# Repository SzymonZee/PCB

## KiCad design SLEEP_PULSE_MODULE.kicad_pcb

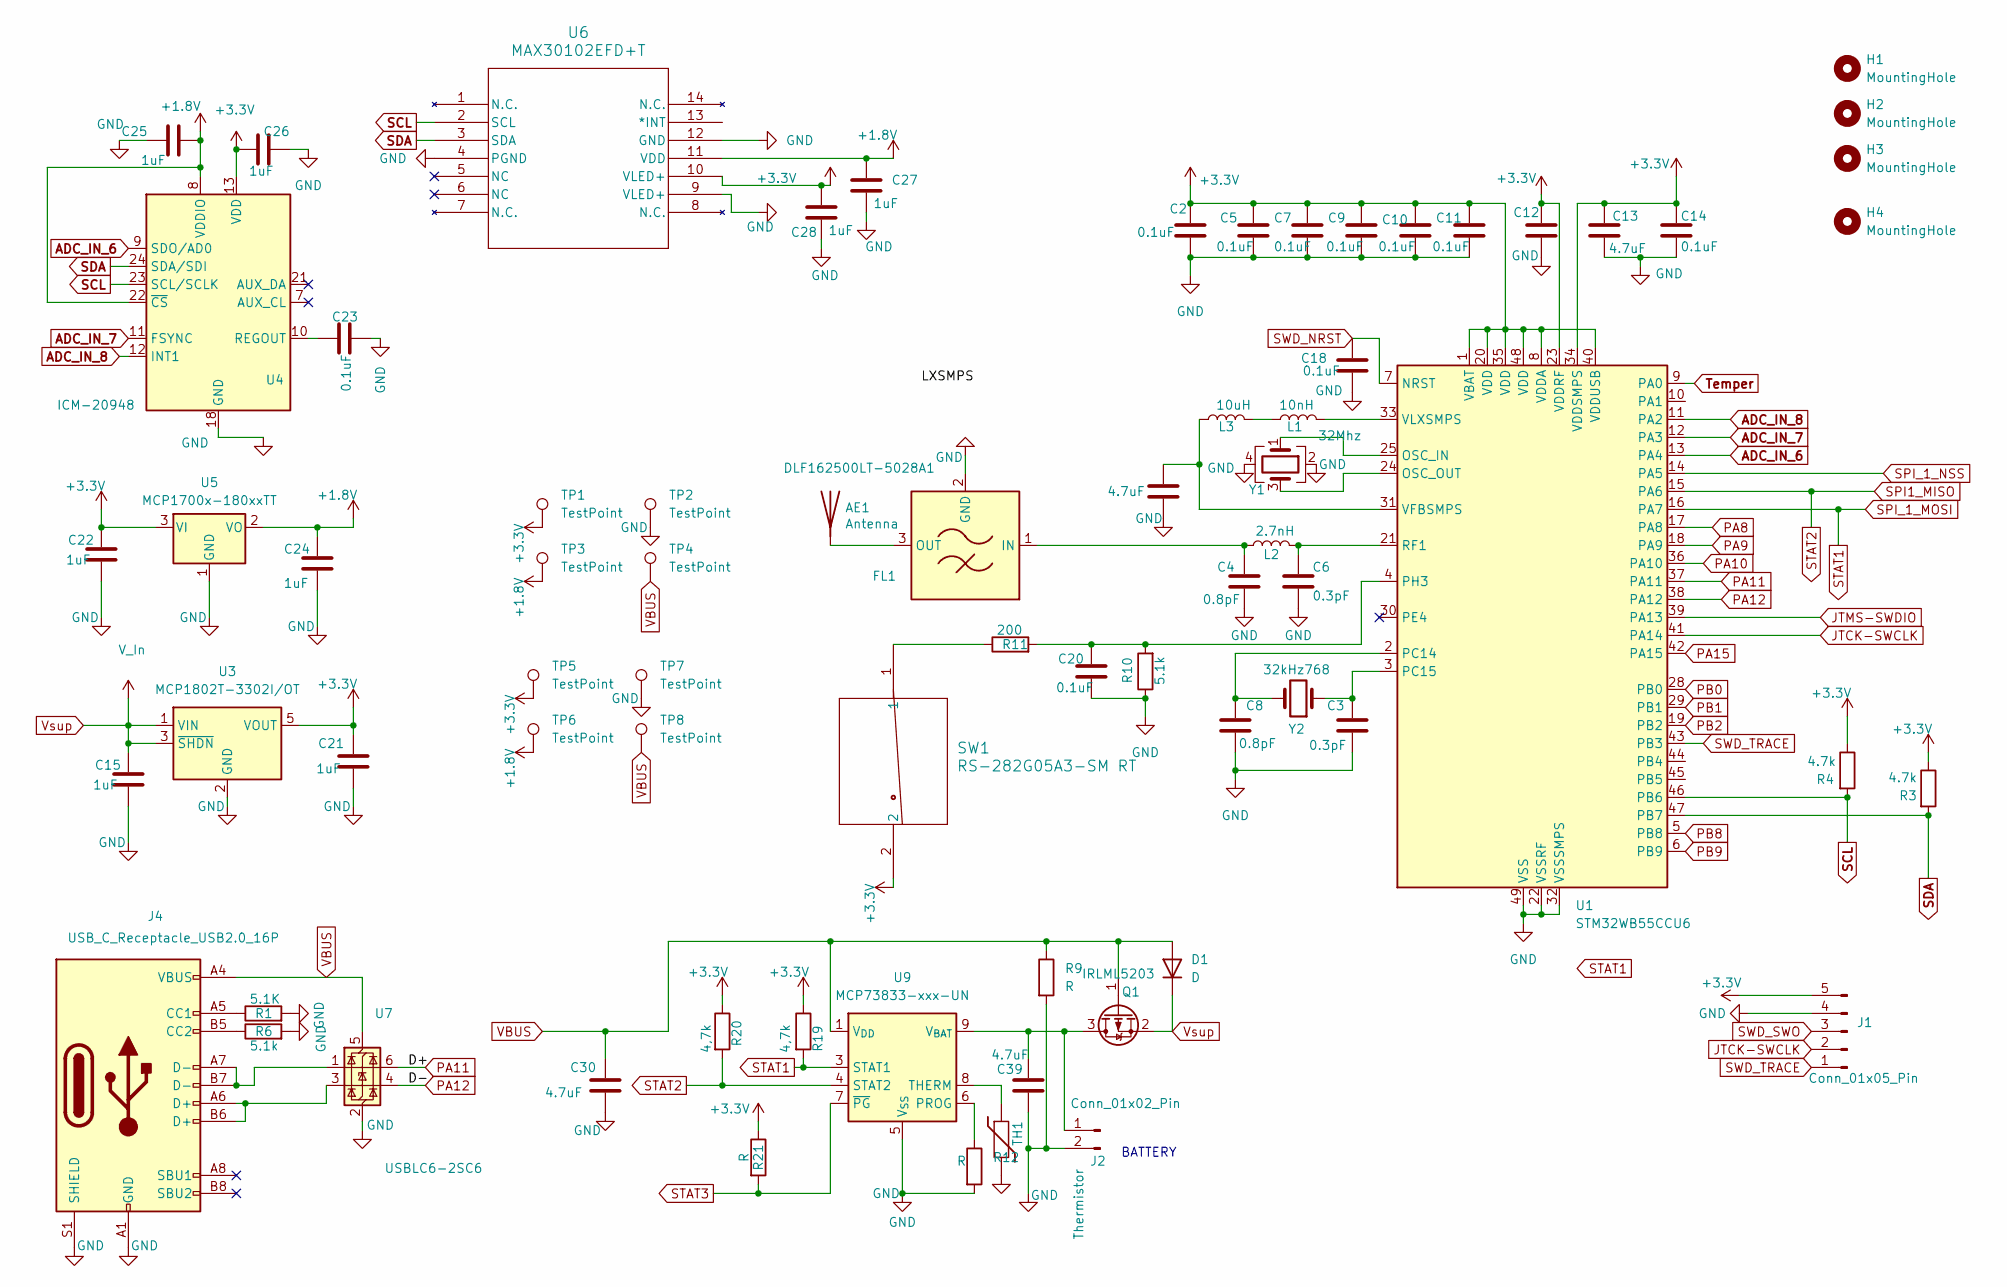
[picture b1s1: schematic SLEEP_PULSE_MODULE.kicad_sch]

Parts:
AE1: Antenna; ANTC3216X140N
C1, C13: 4.7uF; C_0402_1005Metric_Pad0.74x0.62mm_HandSolder
C2, C5, C7, C9, C10, C11, C12, C14, C18, C20, C23: 0.1uF; C_0402_1005Metric_Pad0.74x0.62mm_HandSolder; PARTREV CC0402JRNPO9BN101
C3, C6: 0.3pF; C_0402_1005Metric_Pad0.74x0.62mm_HandSolder
C4, C8: 0.8pF; C_0402_1005Metric_Pad0.74x0.62mm_HandSolder
C15, C21, C22, C24, C25, C26, C27, C28: 1uF; C_0402_1005Metric_Pad0.74x0.62mm_HandSolder
C30, C39: 4.7uF; C_0805_2012Metric_Pad1.18x1.45mm_HandSolder
D1: D; D_SOD-323
FL1: DLF162500LT-5028A1; DLF-4_1P6X0P8
H1, H4: MountingHole; MountingHole_2.2mm_M2
H2, H3: MountingHole
J1: Conn_01x05_Pin
J2: Conn_01x02_Pin; JST_SH_BM02B-SRSS-TB_1x02-1MP_P1.00mm_Vertical
J4: USB_C_Receptacle_USB2.0_16P; USB_C_Receptacle_GCT_USB4105-xx-A_16P_TopMnt_Horizontal
L1: 10nH; C_0402_1005Metric_Pad0.74x0.62mm_HandSolder
L2: 2.7nH; C_0402_1005Metric_Pad0.74x0.62mm_HandSolder
L3: 10uH; L_0805_2012Metric_Pad1.05x1.20mm_HandSolder
Q1: IRLML5203; SOT-23
R1: 5.1K; R_0402_1005Metric_Pad0.72x0.64mm_HandSolder
R3, R4: 4.7k; R_0402_1005Metric_Pad0.72x0.64mm_HandSolder
R6, R10: 5.1k; R_0402_1005Metric_Pad0.72x0.64mm_HandSolder
R9, R12: R; C_0603_1608Metric_Pad1.08x0.95mm_HandSolder
R11: 200; R_0402_1005Metric_Pad0.72x0.64mm_HandSolder
R19, R20: 4,7k; C_0603_1608Metric_Pad1.08x0.95mm_HandSolder
R21: R
SW1: RS-282G05A3-SM RT; RS-282G05A3-SM RT_CNK
TH1: Thermistor; C_0603_1608Metric_Pad1.08x0.95mm_HandSolder
TP1, TP2, TP3, TP4, TP5, TP6, TP7, TP8: TestPoint; TestPoint_Pad_1.0x1.0mm
U1: STM32WB55CCU6; QFN-48-1EP_7x7mm_P0.5mm_EP5.6x5.6mm
U3: MCP1802T-3302I/OT; SOT-23-5
U4: ICM-20948; InvenSense_QFN-24_3x3mm_P0.4mm
U5: MCP1700x-180xxTT; SOT-23
U6: MAX30102EFD+T; 21-1048_F143A5&plus_1_MXM
U7: USBLC6-2SC6; SOT-23-6
U9: MCP73833-xxx-UN; MSOP-10_3x3mm_P0.5mm
Y1: 32Mhz; Crystal_SMD_2016-4Pin_2.0x1.6mm
Y2: 32kHz768; Crystal_SMD_2012-2Pin_2.0x1.2mm

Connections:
+1.8V: C24.1, C25.2, C27.2, TP3.1, TP6.1, U4.8 (VDDIO), U4.22 (~CS), U5.2 (VO), U6.11 (VDD)
+3.3V: C2.1, C5.1, C7.1, C9.1, C10.1, C11.1, C12.1, C13.1, C14.1, C21.1, C22.1, C26.1, C28.2, J1.5, R3.1, R4.1, R19.1, R20.1, R21.1, SW1.2, TP1.1, TP5.1, U1.1 (VBAT), U1.8 (VDDA), U1.20 (VDD), U1.23 (VDDRF), U1.34 (VDDSMPS), U1.35 (VDD), U1.40 (VDDUSB), U1.48 (VDD), U3.5 (VOUT), U4.13 (VDD), U5.3 (VI), U6.10 (VLED+)
ADC_IN_6: U1.13 (PA4), U4.9 (SDO/AD0)
ADC_IN_7: U1.12 (PA3), U4.11 (FSYNC)
ADC_IN_8: U1.11 (PA2), U4.12 (INT1)
GND: C1.1, C2.2, C3.1, C4.1, C5.2, C6.1, C7.2, C8.1, C9.2, C10.2, C11.2, C12.2, C13.2, C14.2, C15.2, C18.2, C20.2, C21.2, C22.2, C23.2, C24.2, C25.1, C26.2, C27.1, C28.1, C30.2, C39.2, FL1.2 (GND), FL1.4 (GND), J1.4, J2.2, J4.A1 (GND), J4.A12 (GND), J4.B1 (GND), J4.B12 (GND), J4.S1 (SHIELD), R1.2, R6.2, R9.2, R10.1, R12.2, TH1.2, TP2.1, TP7.1, U1.22 (VSSRF), U1.32 (VSSSMPS), U1.49 (VSS), U3.2 (GND), U4.18 (GND), U4.20 (GND), U5.1 (GND), U6.4 (PGND), U6.9 (VLED+), U6.12 (GND), U7.2 (GND), U9.5 (V_{SS}), Y1.2, Y1.4
JTCK-SWCLK: J1.2, U1.41 (PA14)
JTMS-SWDIO: U1.39 (PA13)
unnamed: AE1.1 (A), FL1.3 (OUT)
unnamed: C4.2, FL1.1 (IN), L2.1
unnamed: C39.1, J2.1, Q1.3 (D), U9.9 (V_{BAT}), U9.10 (V_{BAT})
unnamed: J4.A5 (CC1), R1.1
unnamed: J4.B5 (CC2), R6.1
unnamed: J4.A6 (D+), J4.B6 (D+), U7.3 (I/O2)
unnamed: J4.A7 (D-), J4.B7 (D-), U7.1 (I/O1)
unnamed: L1.1, L3.2
unnamed: R11.1, SW1.1
unnamed: U1.25 (OSC_IN), Y1.1
unnamed: U1.24 (OSC_OUT), Y1.3
unnamed: C8.2, U1.2 (PC14), Y2.2
unnamed: C3.2, U1.3 (PC15), Y2.1
unnamed: C20.1, R10.2, R11.2, U1.4 (PH3)
unnamed: C6.2, L2.2, U1.21 (RF1)
unnamed: C1.2, L3.1, U1.31 (VFBSMPS)
unnamed: L1.2, U1.33 (VLXSMPS)
unnamed: C23.1, U4.10 (REGOUT)
unnamed: R12.1, U9.6 (PROG)
unnamed: TH1.1, U9.8 (THERM)
PA8: U1.17 (PA8)
PA9: U1.18 (PA9)
PA10: U1.36 (PA10)
PA11: U1.37 (PA11), U7.6 (I/O1)
PA12: U1.38 (PA12), U7.4 (I/O2)
PA15: U1.42 (PA15)
PB0: U1.28 (PB0)
PB1: U1.29 (PB1)
PB2: U1.19 (PB2)
PB8: U1.5 (PB8)
PB9: U1.6 (PB9)
SCL: R4.2, U1.46 (PB6), U4.23 (SCL/SCLK), U6.2 (SCL)
SDA: R3.2, U1.47 (PB7), U4.24 (SDA/SDI), U6.3 (SDA)
SPI1_MISO: R20.2, U1.15 (PA6), U9.4 (STAT2)
SPI_1_MOSI: R19.2, U1.16 (PA7), U9.3 (STAT1)
SPI_1_NSS: U1.14 (PA5)
STAT3: R21.2, U9.7 (~PG)
SWD_NRST: C18.1, U1.7 (NRST)
SWD_TRACE: J1.1, U1.43 (PB3)
Temper: U1.9 (PA0)
VBUS: C30.1, D1.2 (A), J4.A4 (VBUS), J4.A9 (VBUS), J4.B4 (VBUS), J4.B9 (VBUS), Q1.1 (G), R9.1, TP4.1, TP8.1, U7.5 (VBUS), U9.1 (V_{DD}), U9.2 (V_{DD})
Vsup: C15.1, D1.1 (K), Q1.2 (S), U3.1 (VIN), U3.3 (~SHDN)

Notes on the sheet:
BATTERY

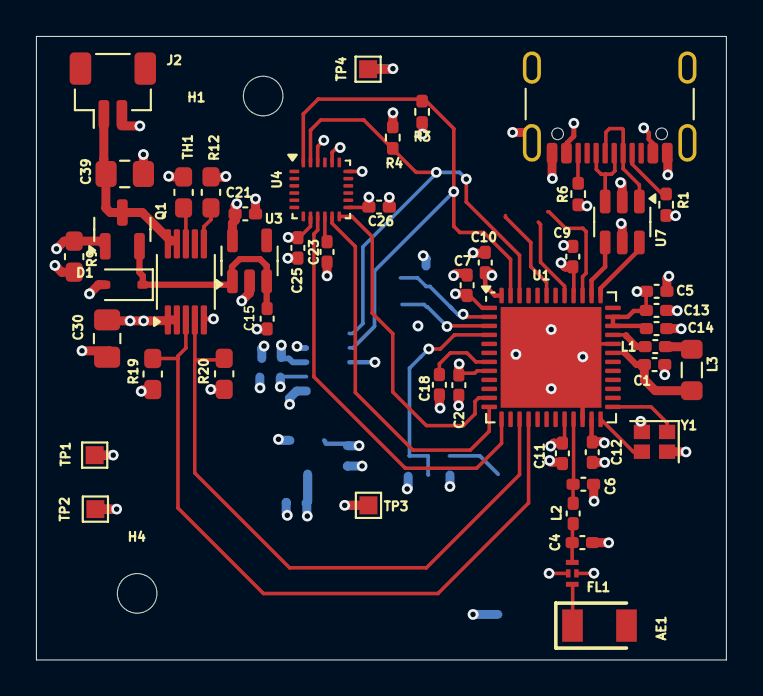
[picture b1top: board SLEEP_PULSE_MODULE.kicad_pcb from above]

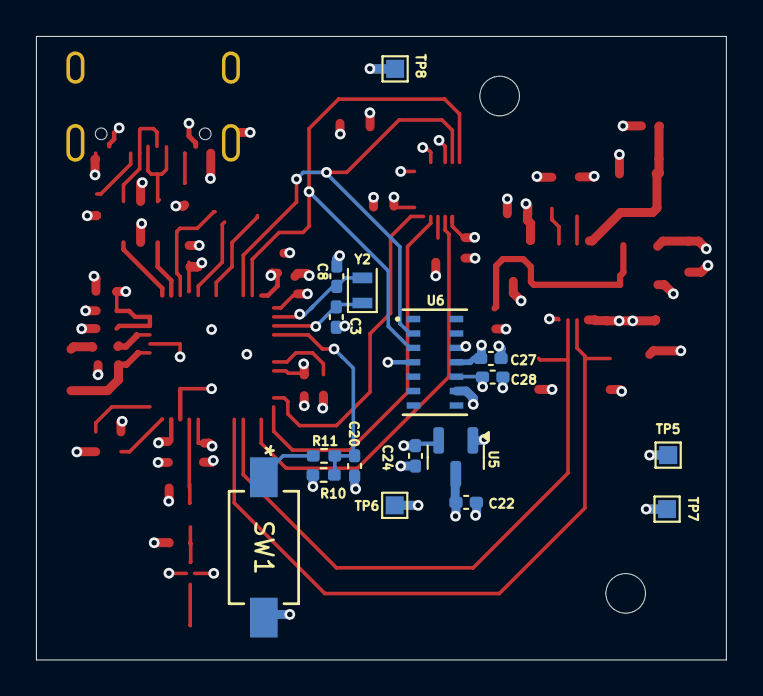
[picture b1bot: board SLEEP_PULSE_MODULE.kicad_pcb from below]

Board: 6 copper layers, 38.3 x 34.6 mm, 67 parts (17 on the bottom side), 35 nets.

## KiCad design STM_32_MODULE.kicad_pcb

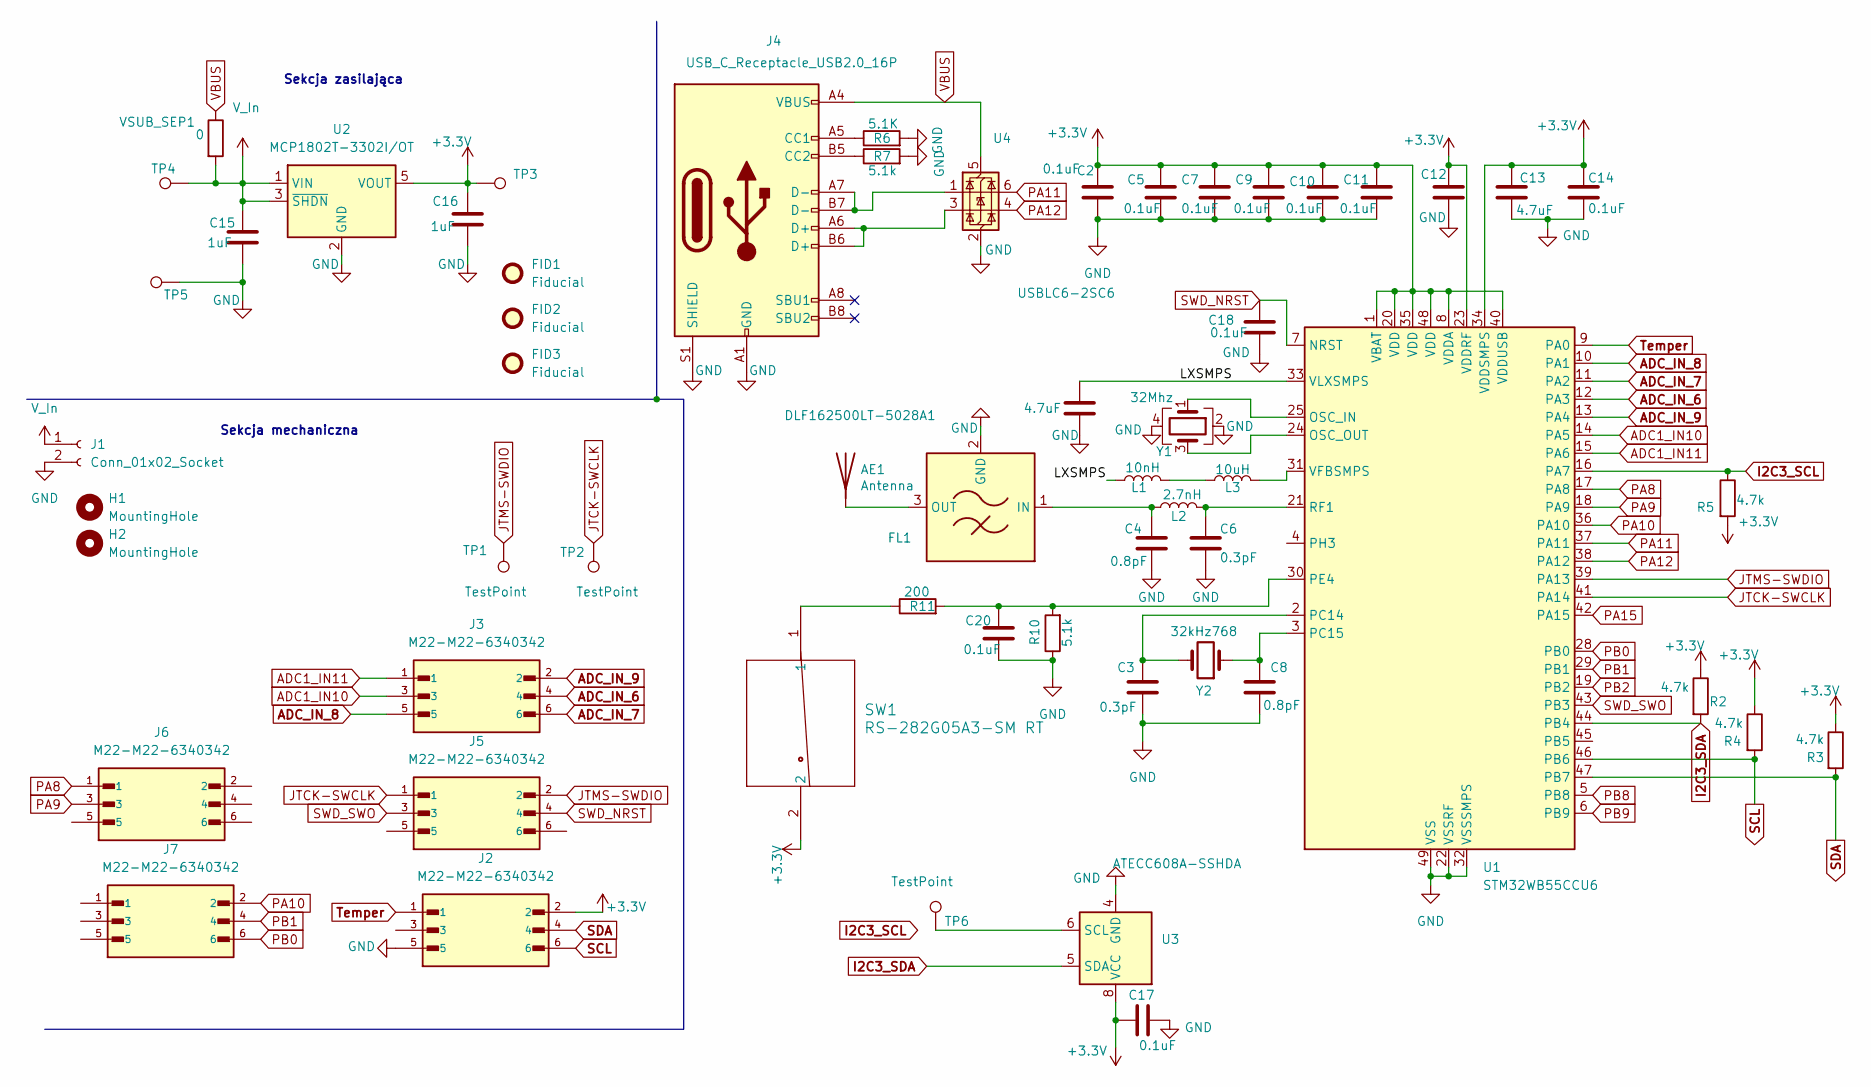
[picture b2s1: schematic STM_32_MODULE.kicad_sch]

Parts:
AE1: Antenna; ANTC3216X140N
C1, C13: 4.7uF; C_0402_1005Metric_Pad0.74x0.62mm_HandSolder
C2, C5, C7, C9, C10, C11, C12, C14, C17, C18, C20: 0.1uF; C_0402_1005Metric_Pad0.74x0.62mm_HandSolder; PARTREV CC0402JRNPO9BN101
C3: 0.3pF; C_0603_1608Metric_Pad1.08x0.95mm_HandSolder
C4: 0.8pF; C_0402_1005Metric_Pad0.74x0.62mm_HandSolder
C6: 0.3pF; C_0402_1005Metric_Pad0.74x0.62mm_HandSolder
C8: 0.8pF; C_0603_1608Metric_Pad1.08x0.95mm_HandSolder
C15, C16: 1uF; C_0402_1005Metric_Pad0.74x0.62mm_HandSolder
FID1, FID2, FID3: Fiducial; Fiducial_0.5mm_Mask1mm
FL1: DLF162500LT-5028A1; DLF-4_1P6X0P8
H1, H2: MountingHole; MountingHole_2.2mm_M2
J1: Conn_01x02_Socket; SM02BSRSSTBLFSN
J2, J3, J5, J6, J7: M22-M22-6340342; HARWIN_M22-6340342
J4: USB_C_Receptacle_USB2.0_16P; USB_C_Receptacle_GCT_USB4105-xx-A_16P_TopMnt_Horizontal
L1: 10nH; C_0402_1005Metric_Pad0.74x0.62mm_HandSolder
L2: 2.7nH; C_0402_1005Metric_Pad0.74x0.62mm_HandSolder
L3: 10uH; L_0805_2012Metric_Pad1.05x1.20mm_HandSolder
R2, R3, R4, R5: 4.7k; R_0402_1005Metric_Pad0.72x0.64mm_HandSolder
R6: 5.1K; R_0402_1005Metric_Pad0.72x0.64mm_HandSolder
R7, R10: 5.1k; R_0402_1005Metric_Pad0.72x0.64mm_HandSolder
R11: 200; R_0402_1005Metric_Pad0.72x0.64mm_HandSolder
SW1: RS-282G05A3-SM RT; RS-282G05A3-SM RT_CNK
TP1, TP2, TP3, TP4, TP5, TP6: TestPoint; TestPoint_Pad_D1.0mm
U1: STM32WB55CCU6; QFN-48-1EP_7x7mm_P0.5mm_EP5.6x5.6mm
U2: MCP1802T-3302I/OT; SOT-23-5
U3: ATECC608A-SSHDA; SOIC-8_3.9x4.9mm_P1.27mm
U4: USBLC6-2SC6; SOT-23-6
VSUB_SEP1: 0; R_0402_1005Metric_Pad0.72x0.64mm_HandSolder
Y1: 32Mhz; Crystal_SMD_2016-4Pin_2.0x1.6mm
Y2: 32kHz768; Crystal_SMD_2012-2Pin_2.0x1.2mm

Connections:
+3.3V: C2.1, C5.1, C7.1, C9.1, C10.1, C11.1, C12.1, C13.1, C14.1, C16.1, C17.1, J2.2, R2.1, R3.1, R4.1, R5.2, SW1.2, TP3.1, U1.1 (VBAT), U1.8 (VDDA), U1.20 (VDD), U1.23 (VDDRF), U1.34 (VDDSMPS), U1.35 (VDD), U1.40 (VDDUSB), U1.48 (VDD), U2.5 (VOUT), U3.8 (VCC)
/LXSMPS: C1.2, L1.1, U1.33 (VLXSMPS)
ADC1_IN10: J3.3, U1.14 (PA5)
ADC1_IN11: J3.1, U1.15 (PA6)
ADC_IN_6: J3.4, U1.12 (PA3)
ADC_IN_7: J3.6, U1.11 (PA2)
ADC_IN_8: J3.5, U1.10 (PA1)
ADC_IN_9: J3.2, U1.13 (PA4)
GND: C1.1, C2.2, C3.1, C4.1, C5.2, C6.1, C7.2, C8.1, C9.2, C10.2, C11.2, C12.2, C13.2, C14.2, C15.2, C16.2, C17.2, C18.2, C20.2, FL1.2 (GND), FL1.4 (GND), J1.2, J2.5, J4.A1 (GND), J4.A12 (GND), J4.B1 (GND), J4.B12 (GND), J4.S1 (SHIELD), R6.2, R7.2, R10.1, TP5.1, U1.22 (VSSRF), U1.32 (VSSSMPS), U1.49 (VSS), U2.2 (GND), U3.4 (GND), U4.2 (GND), Y1.2, Y1.4
I2C3_SDA: R2.2, U1.44 (PB4), U3.5 (SDA)
JTCK-SWCLK: J5.1, TP2.1, U1.41 (PA14)
JTMS-SWDIO: J5.2, TP1.1, U1.39 (PA13)
unnamed: AE1.1 (A), FL1.3 (OUT)
unnamed: C4.2, FL1.1 (IN), L2.1
unnamed: J4.A5 (CC1), R6.1
unnamed: J4.B5 (CC2), R7.1
unnamed: J4.A6 (D+), J4.B6 (D+), U4.3 (I/O2)
unnamed: J4.A7 (D-), J4.B7 (D-), U4.1 (I/O1)
unnamed: L1.2, L3.1
unnamed: R11.1, SW1.1
unnamed: U1.25 (OSC_IN), Y1.1
unnamed: U1.24 (OSC_OUT), Y1.3
unnamed: C3.2, U1.2 (PC14), Y2.2
unnamed: C8.2, U1.3 (PC15), Y2.1
unnamed: C20.1, R10.2, R11.2, U1.30 (PE4)
unnamed: C6.2, L2.2, U1.21 (RF1)
unnamed: L3.2, U1.31 (VFBSMPS)
PA8: J6.1, U1.17 (PA8)
PA9: J6.3, U1.18 (PA9)
PA10: J7.2, U1.36 (PA10)
PA11: U1.37 (PA11), U4.6 (I/O1)
PA12: U1.38 (PA12), U4.4 (I/O2)
PA15: U1.42 (PA15)
PB0: J7.6, U1.28 (PB0)
PB1: J7.4, U1.29 (PB1)
PB2: U1.19 (PB2)
PB8: U1.5 (PB8)
PB9: U1.6 (PB9)
SCL: J2.6, R4.2, U1.46 (PB6)
SDA: J2.4, R3.2, U1.47 (PB7)
SWD_NRST: C18.1, J5.4, U1.7 (NRST)
SWD_SWO: J5.3, U1.43 (PB3)
Temper: J2.1, U1.9 (PA0)
VBUS: J4.A4 (VBUS), J4.A9 (VBUS), J4.B4 (VBUS), J4.B9 (VBUS), U4.5 (VBUS), VSUB_SEP1.1
V_In: C15.1, J1.1, TP4.1, U2.1 (VIN), U2.3 (~SHDN), VSUB_SEP1.2

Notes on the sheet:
Sekcja mechaniczna
Sekcja zasilająca

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
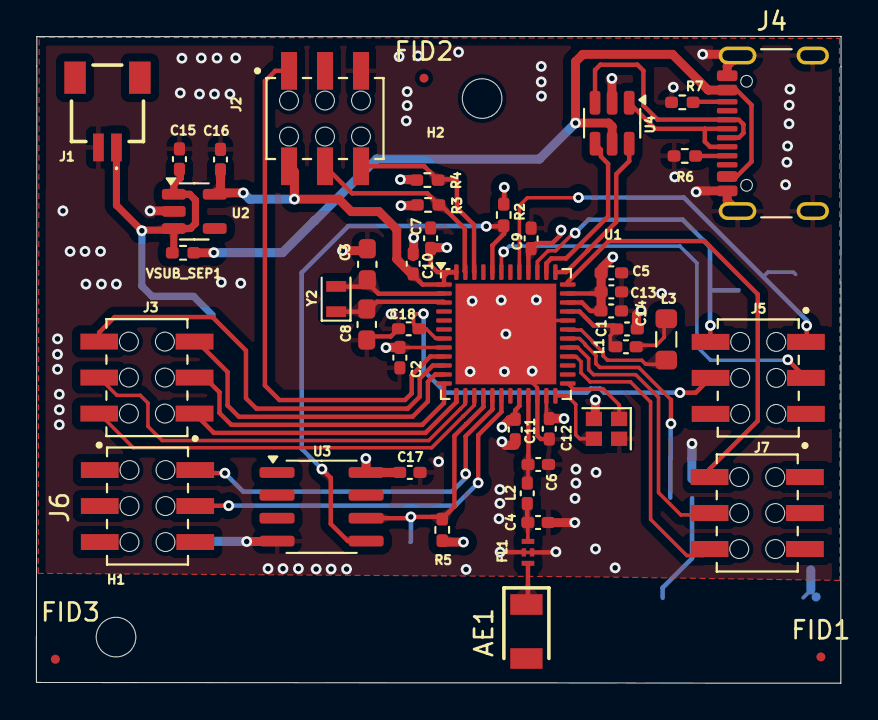
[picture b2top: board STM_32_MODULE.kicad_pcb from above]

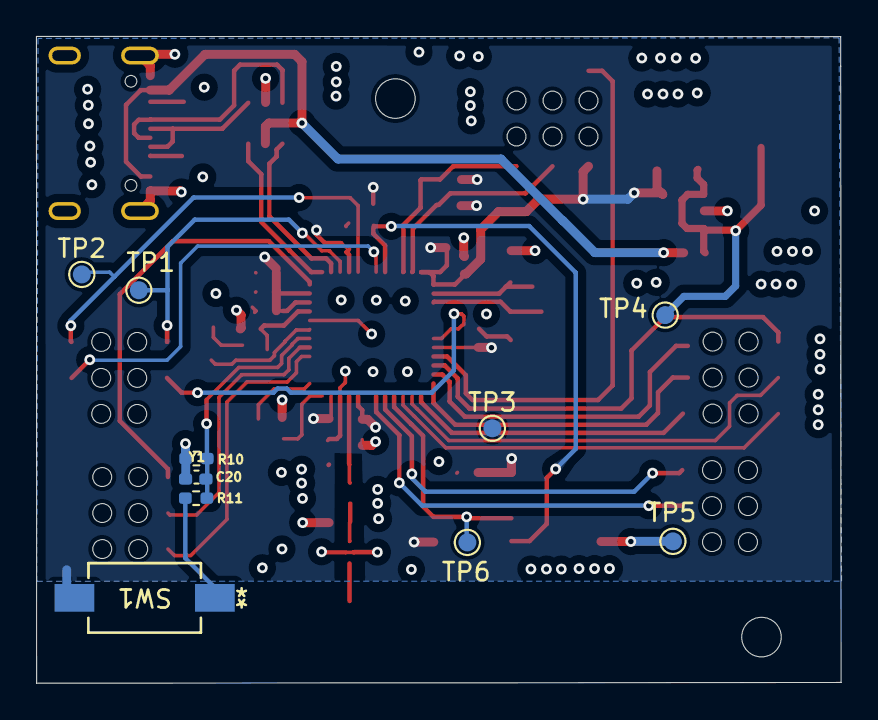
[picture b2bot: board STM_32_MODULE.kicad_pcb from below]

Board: 4 copper layers, 44.7 x 35.9 mm, 58 parts (10 on the bottom side), 42 nets.

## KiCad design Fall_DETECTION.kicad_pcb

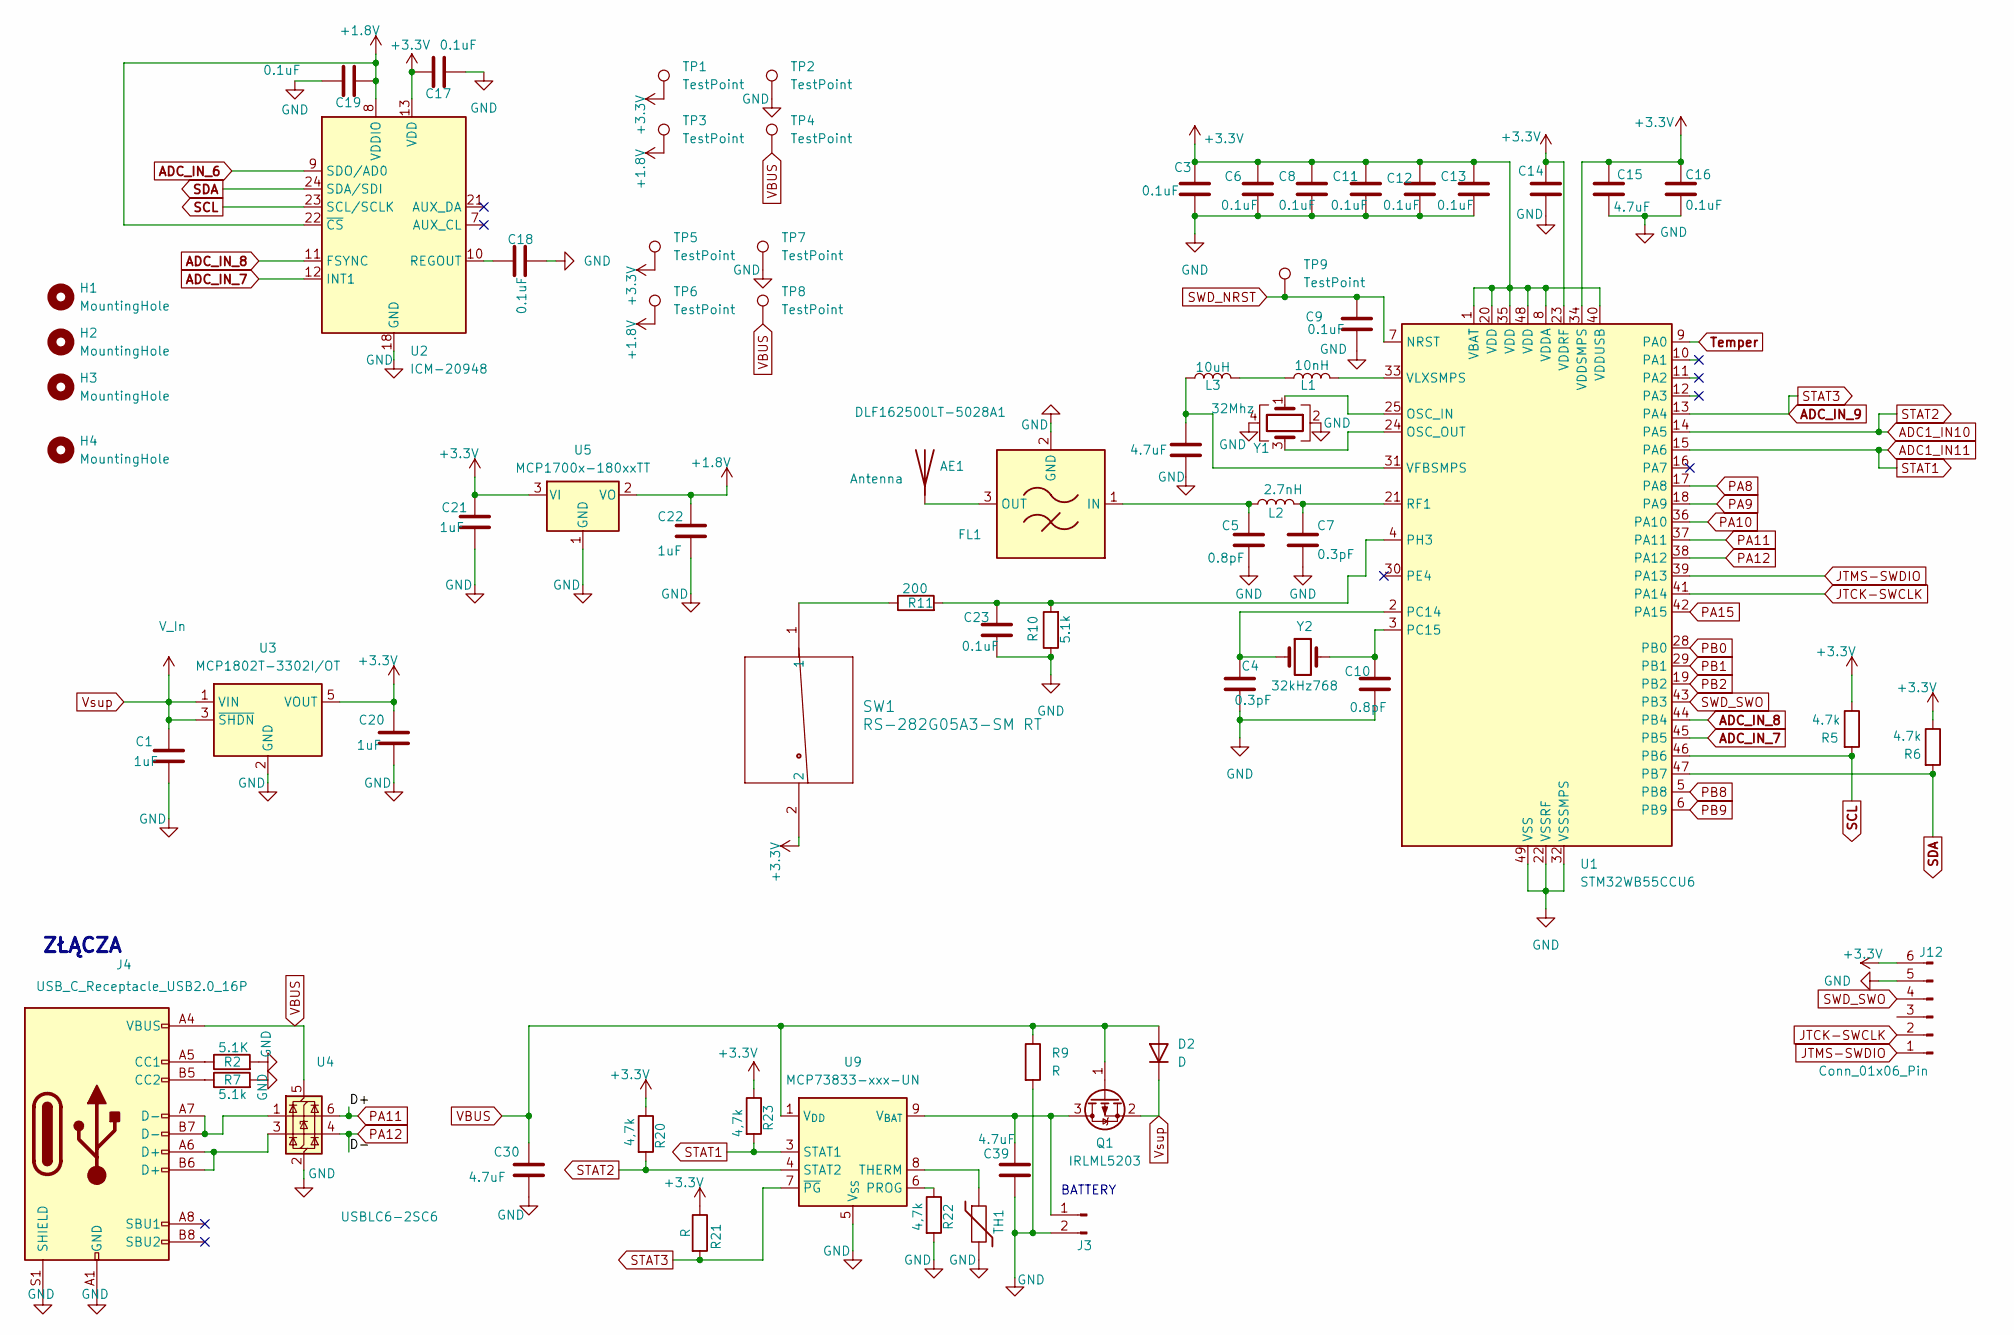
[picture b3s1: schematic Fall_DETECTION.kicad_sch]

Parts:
AE1: Antenna; ANTC3216X140N
C1, C20, C21, C22: 1uF; C_0402_1005Metric_Pad0.74x0.62mm_HandSolder
C2, C15: 4.7uF; C_0402_1005Metric_Pad0.74x0.62mm_HandSolder
C3, C6, C8, C9, C11, C12, C13, C14, C16, C17, C18, C19, C23: 0.1uF; C_0402_1005Metric_Pad0.74x0.62mm_HandSolder; PARTREV CC0402JRNPO9BN101
C4: 0.3pF; C_0603_1608Metric_Pad1.08x0.95mm_HandSolder
C5: 0.8pF; C_0402_1005Metric_Pad0.74x0.62mm_HandSolder
C7: 0.3pF; C_0402_1005Metric_Pad0.74x0.62mm_HandSolder
C10: 0.8pF; C_0603_1608Metric_Pad1.08x0.95mm_HandSolder
C30, C39: 4.7uF; C_0805_2012Metric_Pad1.18x1.45mm_HandSolder
D2: D; D_SOD-323
FL1: DLF162500LT-5028A1; DLF-4_1P6X0P8
H1, H4: MountingHole; MountingHole_2.2mm_M2
H2, H3: MountingHole
J3: Conn_01x02_Pin; JST_SH_BM02B-SRSS-TB_1x02-1MP_P1.00mm_Vertical
J4: USB_C_Receptacle_USB2.0_16P; USB_C_Receptacle_GCT_USB4105-xx-A_16P_TopMnt_Horizontal
J12: Conn_01x06_Pin; PinSocket_2x03_P1.27mm_Vertical_SMD
L1: 10nH; C_0402_1005Metric_Pad0.74x0.62mm_HandSolder
L2: 2.7nH; C_0402_1005Metric_Pad0.74x0.62mm_HandSolder
L3: 10uH; L_0805_2012Metric_Pad1.05x1.20mm_HandSolder
Q1: IRLML5203; SOT-23
R2: 5.1K; R_0402_1005Metric_Pad0.72x0.64mm_HandSolder
R5, R6: 4.7k; R_0402_1005Metric_Pad0.72x0.64mm_HandSolder
R7, R10: 5.1k; R_0402_1005Metric_Pad0.72x0.64mm_HandSolder
R9: R
R11: 200; R_0402_1005Metric_Pad0.72x0.64mm_HandSolder
R20, R23: 4,7k; R_0402_1005Metric_Pad0.72x0.64mm_HandSolder
R21: R; R_0402_1005Metric_Pad0.72x0.64mm_HandSolder
R22: 4,7k; C_0603_1608Metric_Pad1.08x0.95mm_HandSolder
SW1: RS-282G05A3-SM RT; RS-282G05A3-SM RT_CNK-M
TH1: Thermistor; R_0603_1608Metric
TP1, TP2, TP3, TP4, TP5, TP6, TP7, TP8, TP9: TestPoint; TestPoint_Pad_1.0x1.0mm
U1: STM32WB55CCU6; QFN-48-1EP_7x7mm_P0.5mm_EP5.6x5.6mm
U2: ICM-20948; InvenSense_QFN-24_3x3mm_P0.4mm
U3: MCP1802T-3302I/OT; SOT-23-5
U4: USBLC6-2SC6; SOT-23-6
U5: MCP1700x-180xxTT; SOT-23
U9: MCP73833-xxx-UN; MSOP-10_3x3mm_P0.5mm
Y1: 32Mhz; Crystal_SMD_2016-4Pin_2.0x1.6mm
Y2: 32kHz768; Crystal_SMD_2012-2Pin_2.0x1.2mm

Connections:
+1.8V: C19.1, C22.1, TP3.1, TP6.1, U2.8 (VDDIO), U2.22 (~CS), U5.2 (VO)
+3.3V: C3.1, C6.1, C8.1, C11.1, C12.1, C13.1, C14.1, C15.1, C16.1, C17.2, C20.1, C21.1, J12.6, R5.1, R6.1, R20.1, R21.1, R23.1, SW1.2, TP1.1, TP5.1, U1.1 (VBAT), U1.8 (VDDA), U1.20 (VDD), U1.23 (VDDRF), U1.34 (VDDSMPS), U1.35 (VDD), U1.40 (VDDUSB), U1.48 (VDD), U2.13 (VDD), U3.5 (VOUT), U5.3 (VI)
ADC1_IN10: R20.2, U1.14 (PA5), U9.4 (STAT2)
ADC1_IN11: R23.2, U1.15 (PA6), U9.3 (STAT1)
ADC_IN_6: U2.9 (SDO/AD0)
ADC_IN_7: U1.45 (PB5), U2.12 (INT1)
ADC_IN_8: U1.44 (PB4), U2.11 (FSYNC)
ADC_IN_9: R21.2, U1.13 (PA4), U9.7 (~PG)
GND: C1.2, C2.1, C3.2, C4.1, C5.1, C6.2, C7.1, C8.2, C9.2, C10.1, C11.2, C12.2, C13.2, C14.2, C15.2, C16.2, C17.1, C18.2, C19.2, C20.2, C21.2, C22.2, C23.2, C30.2, C39.2, FL1.2 (GND), FL1.4 (GND), J3.2, J4.A1 (GND), J4.A12 (GND), J4.B1 (GND), J4.B12 (GND), J4.S1 (SHIELD), J12.5, R2.2, R7.2, R9.2, R10.1, R22.2, TH1.2, TP2.1, TP7.1, U1.22 (VSSRF), U1.32 (VSSSMPS), U1.49 (VSS), U2.18 (GND), U2.20 (GND), U3.2 (GND), U4.2 (GND), U5.1 (GND), U9.5 (V_{SS}), Y1.2, Y1.4
JTCK-SWCLK: J12.2, U1.41 (PA14)
JTMS-SWDIO: J12.1, U1.39 (PA13)
unnamed: AE1.1 (A), FL1.3 (OUT)
unnamed: C5.2, FL1.1 (IN), L2.1
unnamed: C39.1, J3.1, Q1.3 (D), U9.9 (V_{BAT}), U9.10 (V_{BAT})
unnamed: J4.A5 (CC1), R2.1
unnamed: J4.B5 (CC2), R7.1
unnamed: J4.A6 (D+), J4.B6 (D+), U4.3 (I/O2)
unnamed: J4.A7 (D-), J4.B7 (D-), U4.1 (I/O1)
unnamed: L1.1, L3.2
unnamed: R11.1, SW1.1
unnamed: U1.25 (OSC_IN), Y1.1
unnamed: U1.24 (OSC_OUT), Y1.3
unnamed: C4.2, U1.2 (PC14), Y2.1
unnamed: C10.2, U1.3 (PC15), Y2.2
unnamed: C23.1, R10.2, R11.2, U1.4 (PH3)
unnamed: C7.2, L2.2, U1.21 (RF1)
unnamed: C2.2, L3.1, U1.31 (VFBSMPS)
unnamed: L1.2, U1.33 (VLXSMPS)
unnamed: C18.1, U2.10 (REGOUT)
unnamed: R22.1, U9.6 (PROG)
unnamed: TH1.1, U9.8 (THERM)
PA8: U1.17 (PA8)
PA9: U1.18 (PA9)
PA10: U1.36 (PA10)
PA11: U1.37 (PA11), U4.6 (I/O1)
PA12: U1.38 (PA12), U4.4 (I/O2)
PA15: U1.42 (PA15)
PB0: U1.28 (PB0)
PB1: U1.29 (PB1)
PB2: U1.19 (PB2)
PB8: U1.5 (PB8)
PB9: U1.6 (PB9)
SCL: R5.2, U1.46 (PB6), U2.23 (SCL/SCLK)
SDA: R6.2, U1.47 (PB7), U2.24 (SDA/SDI)
SWD_NRST: C9.1, TP9.1, U1.7 (NRST)
SWD_SWO: J12.4, U1.43 (PB3)
Temper: U1.9 (PA0)
VBUS: C30.1, D2.2 (A), J4.A4 (VBUS), J4.A9 (VBUS), J4.B4 (VBUS), J4.B9 (VBUS), Q1.1 (G), R9.1, TP4.1, TP8.1, U4.5 (VBUS), U9.1 (V_{DD}), U9.2 (V_{DD})
Vsup: C1.1, D2.1 (K), Q1.2 (S), U3.1 (VIN), U3.3 (~SHDN)

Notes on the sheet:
ZŁĄCZA
BATTERY

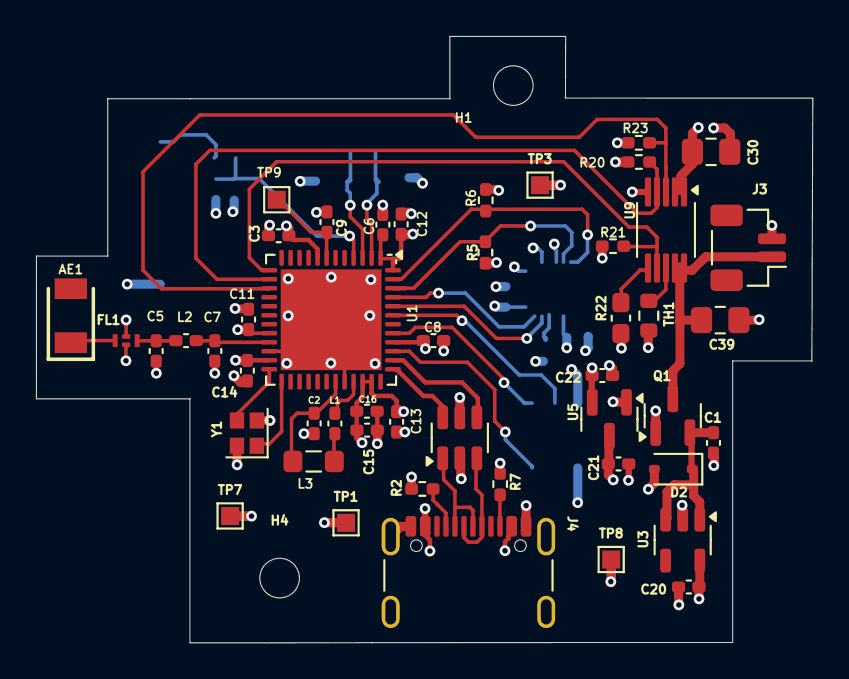
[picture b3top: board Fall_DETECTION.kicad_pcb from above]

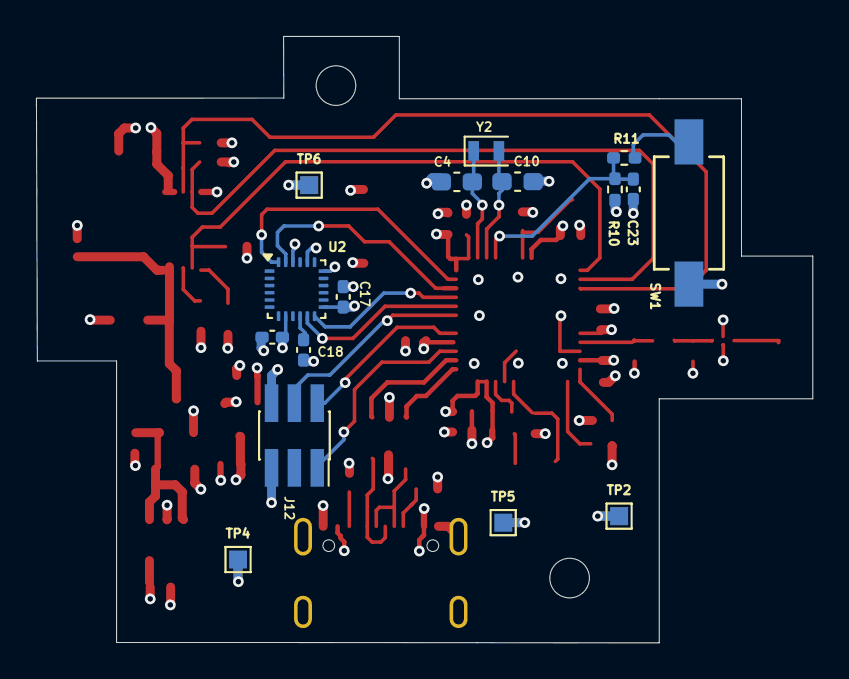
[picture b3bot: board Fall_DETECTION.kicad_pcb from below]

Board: 6 copper layers, 43.1 x 33.7 mm, 66 parts (16 on the bottom side), 38 nets.
